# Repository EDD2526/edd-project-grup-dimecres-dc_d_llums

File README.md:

# Projecte Llums Cotxe

> **Autors:** Marcel Lleonart, Eric Ruiz, Josep Leyva
> **Versió:** 1.1
> **Eina de disseny:** KiCad 9.0 o superior

---

##  Objectiu

Desenvolupar un **sistema de control de llums per a un automòbil a escala de projecte**, gestionat mitjançant un microcontrolador. El sistema integra els principals subsistemes d'il·luminació d'un vehicle i permet el seu control manual i automàtic.

### Funcions principals

* Llums diürnes (**DRL**)
* Intermitents esquerre i dret
* Llums de creuament
* Llums de carretera
* Activació automàtica segons la llum ambiental

Cada canal incorpora:

* Etapa de potència amb MOSFET
* Resistència de gate i pull-down
* Control directe des del microcontrolador mitjançant GPIO

---

##  Diagrama de blocs

---

##  Descripció funcional dels blocs

###  Microcontrolador – PIC18F26Q83

Coordina tots els subsistemes de llum, processa les entrades dels sensors i gestiona les comunicacions externes. Disposa d'interfícies **CAN**, **I2C** i **USART** per a expansió, diagnosi i depuració.

###  Driver de llums diürnes (DRL)

Controla l'encesa automàtica de les llums diürnes mitjançant un MOSFET **AO3400A**. L'activació es realitza segons la lectura del sensor de llum ambiental.

###  Driver d'intermitents

Gestiona els intermitents esquerre i dret. El parpelleig es genera per programari utilitzant temporitzadors interns del microcontrolador.

###  Driver de llums de creuament

Permet el control ON/OFF de les llums de creuament amb protecció elèctrica individual.

###  Driver de llums de carretera

Controla les llums de carretera amb protecció mitjançant fusible. Compatible amb càrregues LED o halògenes de baixa potència.

### Sensor de llum ambiental

Mesura la il·luminació exterior i permet l'activació automàtica de les llums diürnes o altres funcions programades.

---

##  Especificacions tècniques

| Paràmetre              | Valor                                               |
| ---------------------- | --------------------------------------------------- |
| Alimentació principal  | 12 Vcc                                              |
| Alimentació lògica     | 3.3 V regulats                                      |
| Microcontrolador       | Pic24hj128gp502                                     |
| Comunicacions          | CAN, I2C, USART                                     |
| MOSFET de potència     | AO3400A (canal N, logic-level)                      |
| Nivell de control GPIO | 3.3 V                                               |
| Protecció              |resistència de gate + pull-down                      |

---

##  Assignació de GPIO

| Senyal            | Funció                         |
| ----------------- | ------------------------------ |
| `DRL_CTRL`        | Control de llums diürnes       |
| `TURN_LEFT_CTRL`  | Intermitent esquerre           |
| `TURN_RIGHT_CTRL` | Intermitent dret               |
| `LOW_BEAM_CTRL`   | Llums de creuament             |
| `HI_BEAM_CTRL`    | Llums de carretera             |
| `LIGHT_INT`       | Interrupció del sensor de llum |

---

##  Funcionalitats implementades

* Activació automàtica de les DRL segons la llum ambiental
* Control independent de llums de creuament i carretera
* Interfície de depuració per USART
* Arquitectura preparada per integració en xarxa CAN

---

##  Llista de materials (BOM)

| Component                     | Valor / Model              | Encapsulat         | Quantitat |
| ----------------------------- | -------------------------- | ------------------ | --------: |
| Microcontrolador              | Pic24hj128gp502            | SOIC-28            |         1 |
| MOSFET canal N                | AO3400A                    | SOT-23             |         8 |
| Regulador lineal              | LM1117-5.0                 | TO-252             |         1 |
| Resonador / Cristall          | 8 MHz                      | HC-49 o equivalent |         1 |
| Inductor                      | 33 µH                      | Radial             |         1 |
| Díodes de protecció           | Rectificador               | DO-201AD           |         9 |
| Condensadors de desacoblament | 100 nF                     | 0805               |         7 |
| Condensadors                  | 10 µF                      | 0805               |         3 |
| Condensador electrolític      | 680 µF                     | Radial             |         1 |
| Condensadors                  | 33 pF                      | 0805               |         2 |
| Condensador                   | 4.7 nF                     | 0805               |         1 |
| Resistències                  | 100 Ω                      | 0805               |         8 |
| Resistències                  | 10 kΩ                      | 0805               |  Diverses |
| Borns de connexió             | 2 vies, pas 5.08 mm        | Terminal Block     |        11 |
| Connector ICSP                | Programació PIC            | 2x03, 2.54 mm      |         1 |
| Interruptors SPDT             | Selector                   | Through-hole       |         5 |
| Polsador                      | Reset / funció             | 6 mm               |         1 |
| Sensor de llum                | TSL2561 (o equivalent I2C) | SMD                |         1 |

> **Nota:** La quantitat exacta d'alguns components passius pot variar segons la revisió del disseny i les opcions de muntatge.

---

##  Programació i configuració

### Perifèrics utilitzats

* GPIO digitals per al control de sortides
* I2C per al sensor de llum
* USART per a depuració i diagnosi
* CAN per a futures ampliacions

---

##  Proteccions incorporades

* Resistència sèrie a la gate dels MOSFET
* Resistència pull-down per evitar activacions espúries
* Filtrat de l'alimentació mitjançant condensadors de desacoblament
* Protecció davant transitoris de commutació

---

##  Aplicacions

Aquest projecte és ideal per a:

* Maquetes i prototips d'automoció
* Sistemes d'il·luminació intel·ligents
* Pràctiques de microcontroladors i electrònica de potència
* Desenvolupament de mòduls electrònics per automoció

---

##  Estat del projecte

**Versió actual:** 1.5

* ✅ Esquemàtic completat
* 🔄 PCB en desenvolupament i validació
* ✔️ BOM inicial verificada

---

##  Llicència

Aquest projecte ha estat desenvolupat amb finalitats educatives i acadèmiques.

---

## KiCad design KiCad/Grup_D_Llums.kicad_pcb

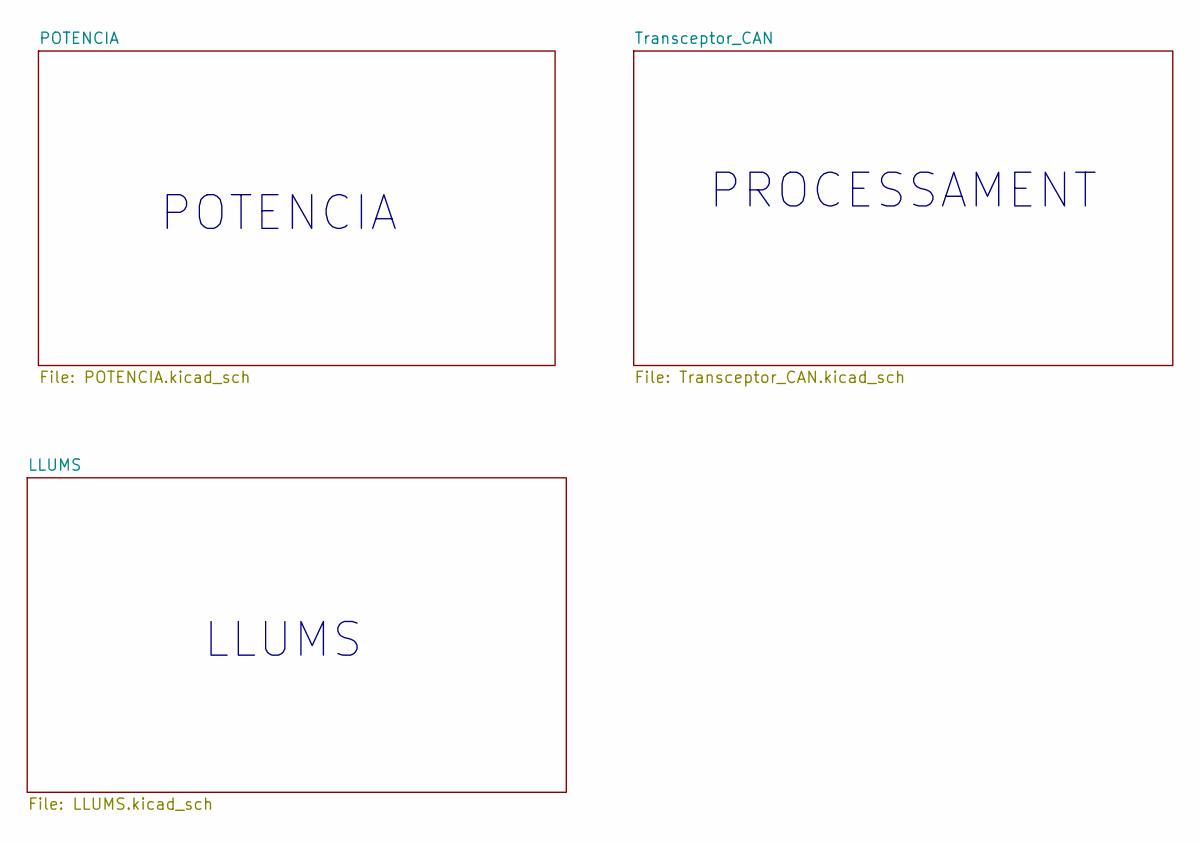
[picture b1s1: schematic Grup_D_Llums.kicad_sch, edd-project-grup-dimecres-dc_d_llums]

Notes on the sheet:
PROCESSAMENT
LLUMS
POTENCIA

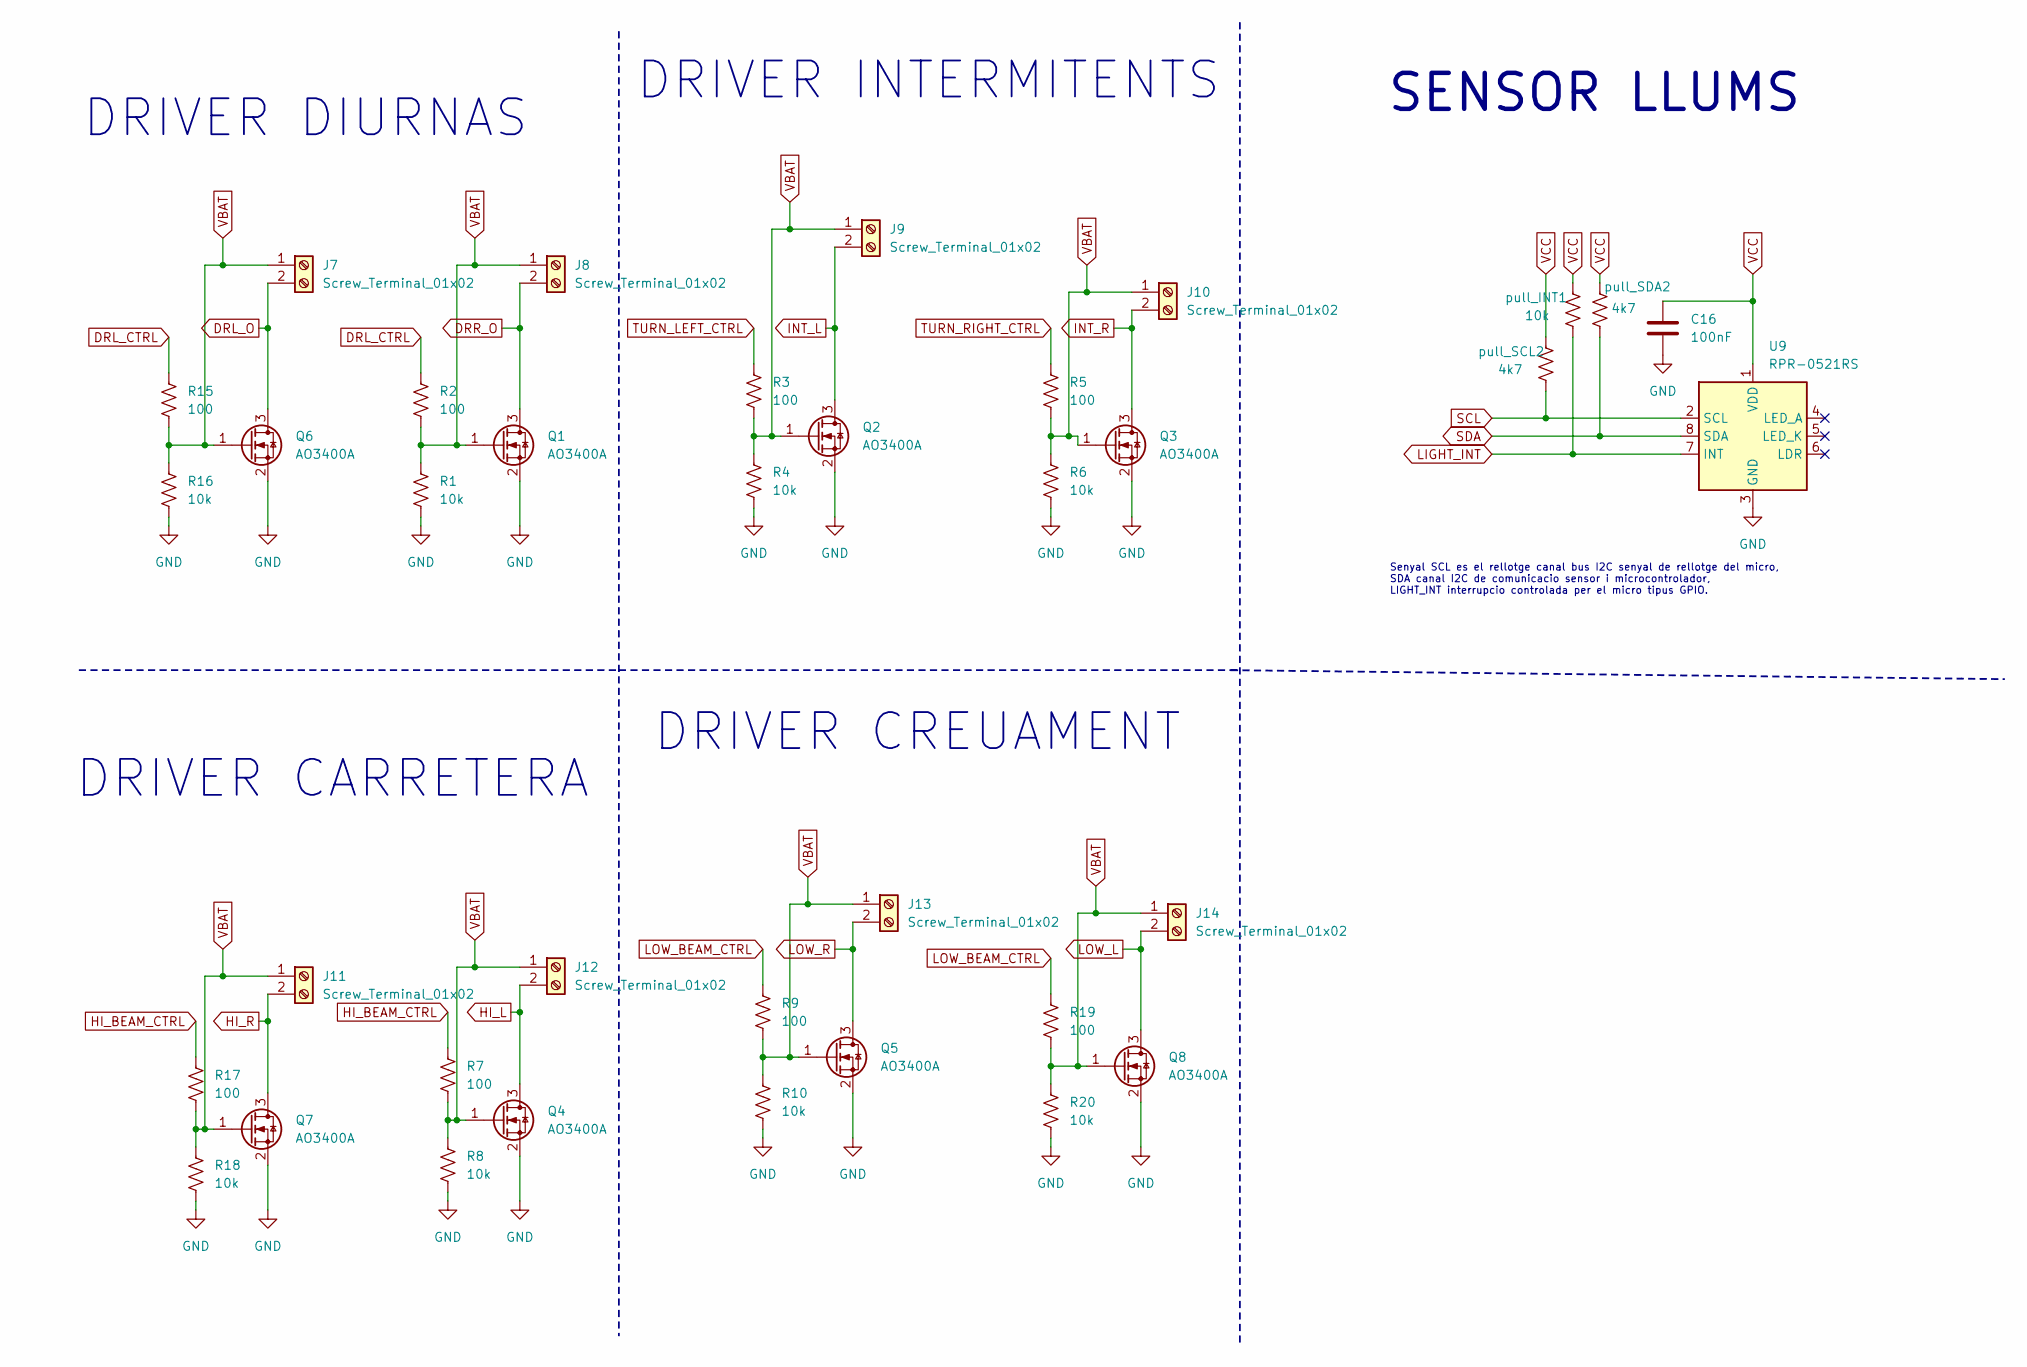
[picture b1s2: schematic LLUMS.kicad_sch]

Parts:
C16: 100nF; C_0805_2012Metric
J7, J8, J9, J10, J11, J12, J13, J14: Screw_Terminal_01x02; TerminalBlock_Phoenix_MKDS-1,5-2-5.08_1x02_P5.08mm_Horizont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
Q1, Q2, Q3, Q4, Q5, Q6, Q7, Q8: AO3400A; SOT-23
R1, R4, R6, R8, R10, R16, R18, R20: 10k; R_0805_2012Metric
R2, R3, R5, R7, R9, R15, R17, R19: 100; R_0805_2012Metric
U9: RPR-0521RS; Rohm_RPR-0521RS
pull_INT1: 10k; R_0805_2012Metric
pull_SCL2: 4k7; R_0805_2012Metric
pull_SDA2: 4k7; R_0805_2012Metric

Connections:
DRL_CTRL: R2.1, R15.1; also elsewhere on the board
DRL_O: J7.2, Q6.3 (D)
DRR_O: J8.2, Q1.3 (D)
GND: C16.2, Q1.2 (S), Q2.2 (S), Q3.2 (S), Q4.2 (S), Q5.2 (S), Q6.2 (S), Q7.2 (S), Q8.2 (S), R1.2, R4.2, R6.2, R8.2, R10.2, R16.2, R18.2, R20.2, U9.3 (GND); also elsewhere on the board
HI_BEAM_CTRL: R7.1, R17.1; also elsewhere on the board
HI_L: J12.2, Q4.3 (D)
HI_R: J11.2, Q7.3 (D)
INT_L: J9.2, Q2.3 (D)
INT_R: J10.2, Q3.3 (D)
LIGHT_INT: U9.7 (INT), pull_INT1.2; also elsewhere on the board
LOW_BEAM_CTRL: R9.1, R19.1; also elsewhere on the board
LOW_L: J14.2, Q8.3 (D)
LOW_R: J13.2, Q5.3 (D)
SCL: U9.2 (SCL), pull_SCL2.2; also elsewhere on the board
SDA: U9.8 (SDA), pull_SDA2.2; also elsewhere on the board
TURN_LEFT_CTRL: R3.1; also elsewhere on the board
TURN_RIGHT_CTRL: R5.1; also elsewhere on the board
VBAT: J7.1, J8.1, J9.1, J10.1, J11.1, J12.1, J13.1, J14.1, Q1.1 (G), Q2.1 (G), Q3.1 (G), Q4.1 (G), Q5.1 (G), Q6.1 (G), Q7.1 (G), Q8.1 (G), R1.1, R2.2, R3.2, R4.1, R5.2, R6.1, R7.2, R8.1, R9.2, R10.1, R15.2, R16.1, R17.2, R18.1, R19.2, R20.1; also elsewhere on the board
VCC: C16.1, U9.1 (VDD), pull_INT1.1, pull_SCL2.1, pull_SDA2.1; also elsewhere on the board

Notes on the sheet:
DRIVER INTERMITENTS
SENSOR LLUMS
DRIVER CREUAMENT
DRIVER DIURNAS
DRIVER CARRETERA
Senyal SCL es el rellotge canal bus I2C senyal de rellotge del micro, SDA canal I2C de comunicacio sensor i microcontrolador, LIGHT_INT interrupcio controlada per el micro tipus GPIO.

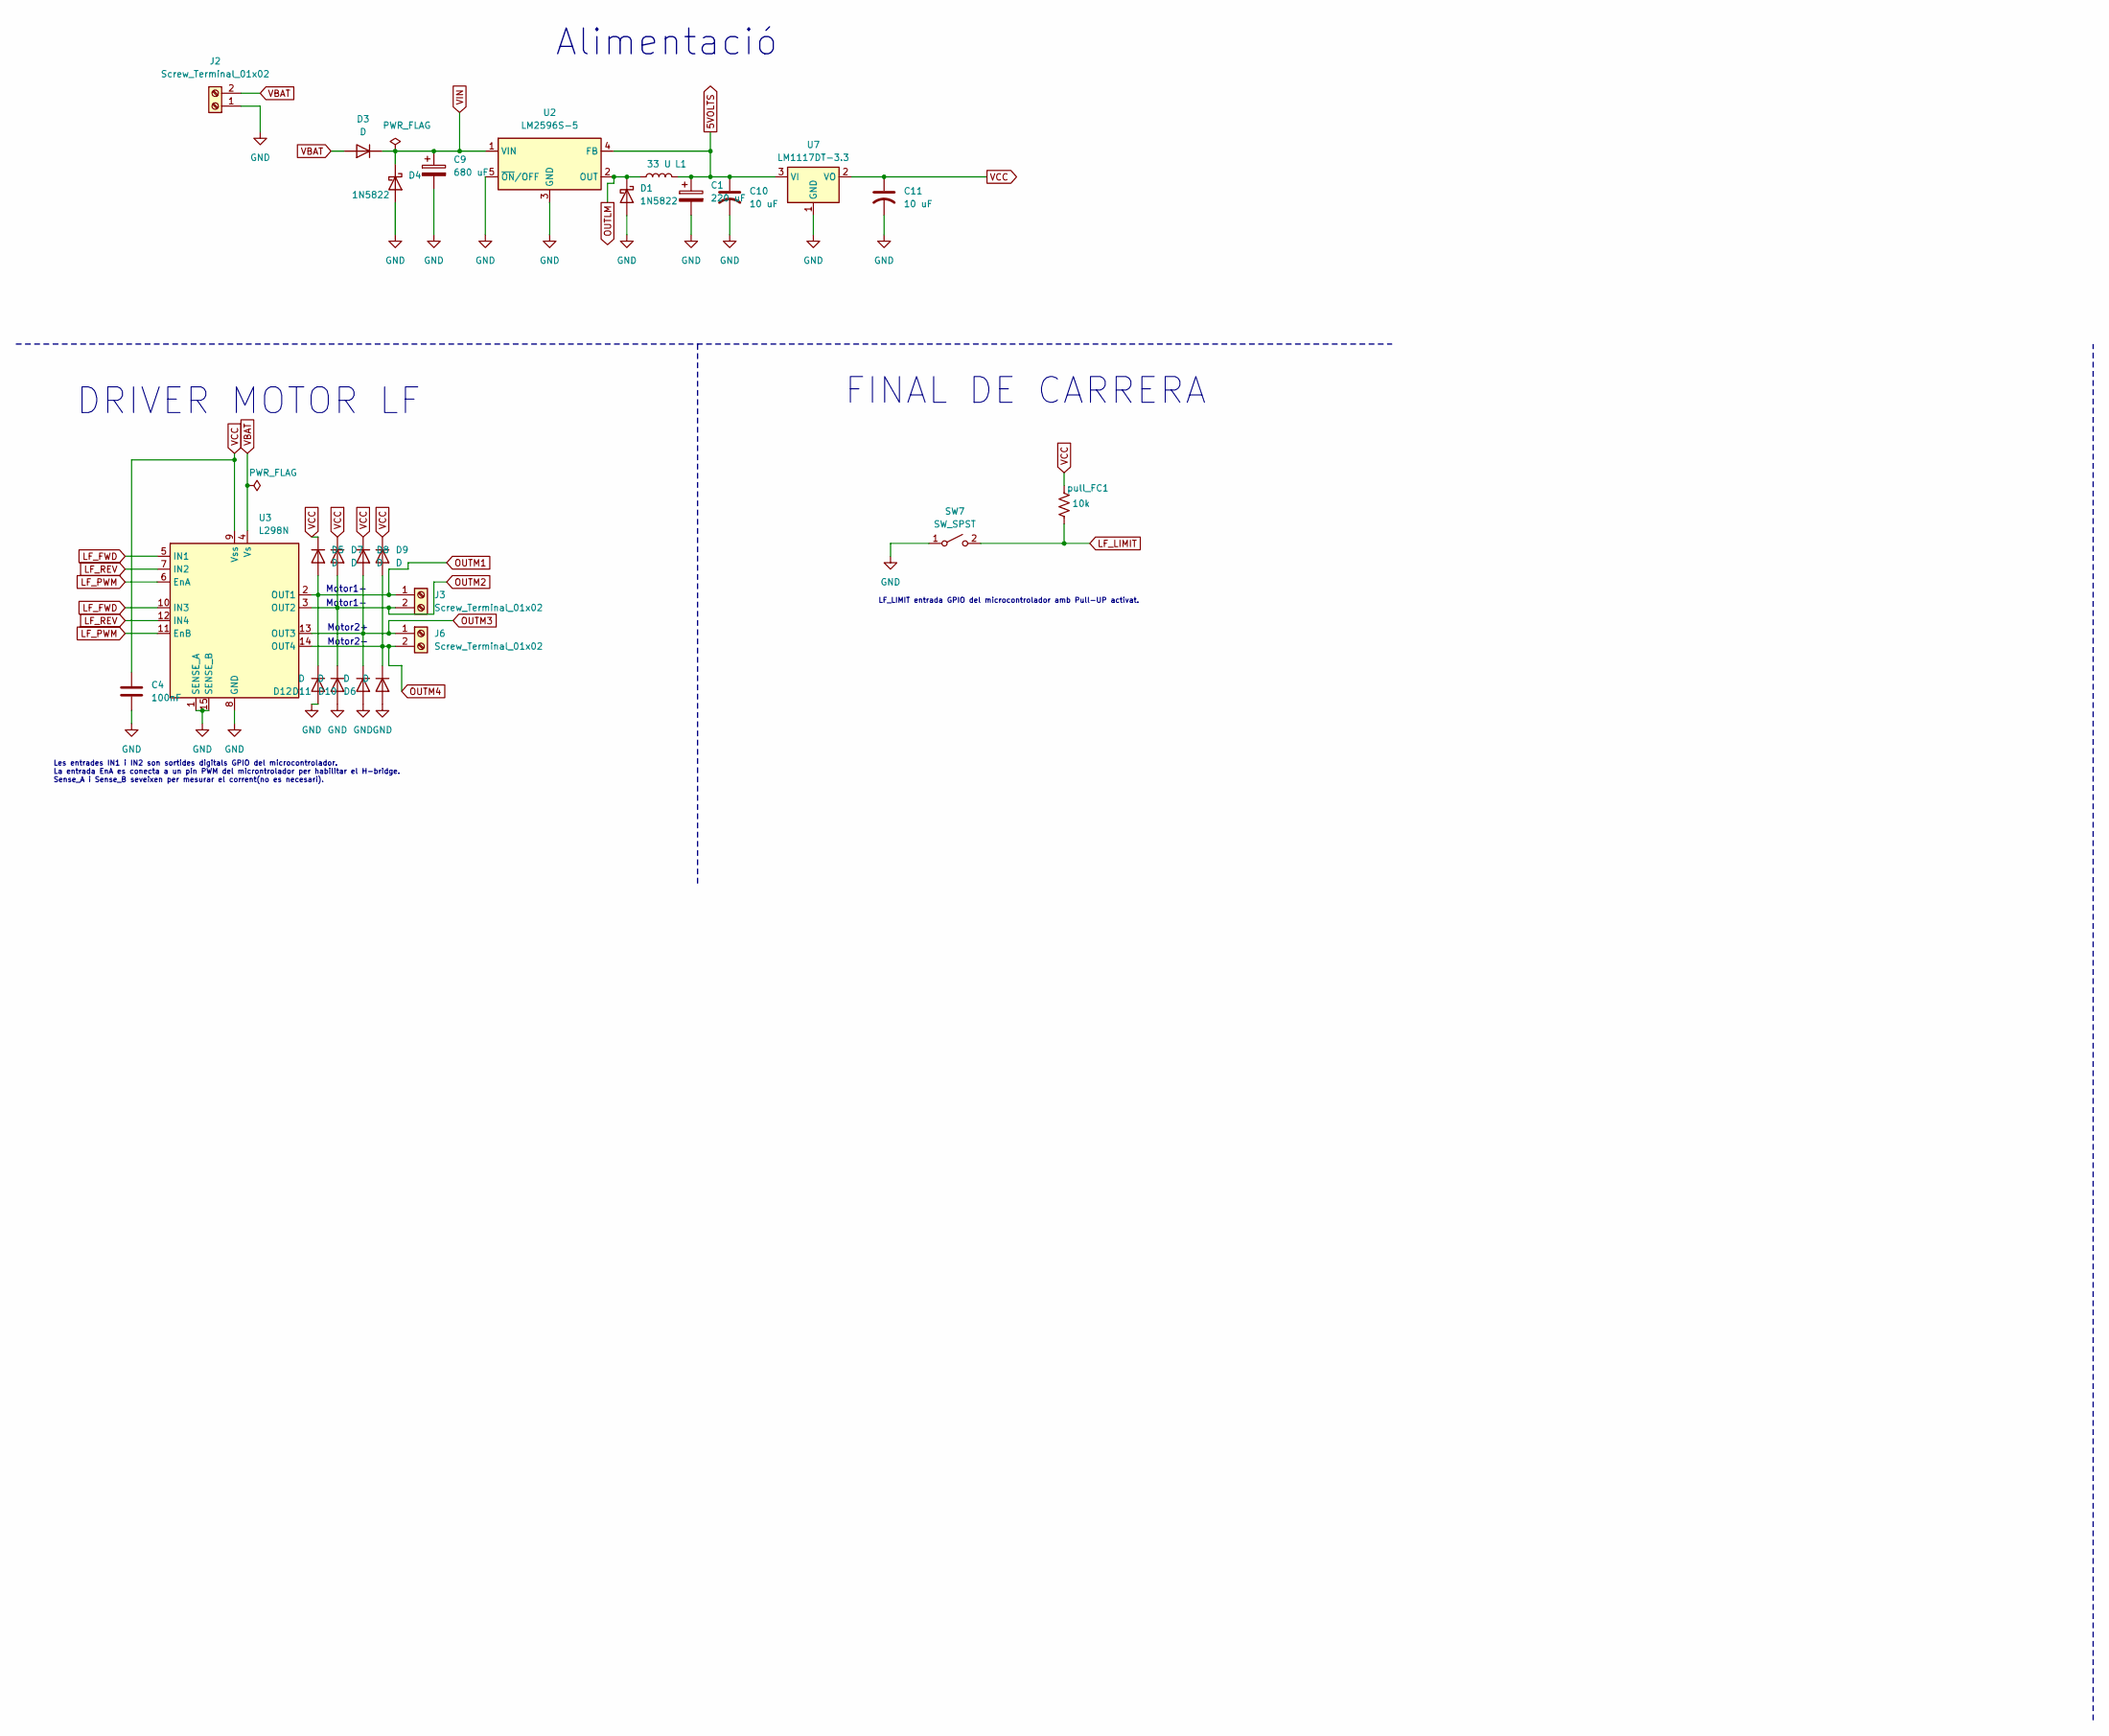
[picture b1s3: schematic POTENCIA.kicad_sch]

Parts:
C1: 220 uF; CP_Radial_D8.0mm_P3.50mm
C4: 100nF; C_0805_2012Metric
C9: 680 uF; CP_Radial_D10.0mm_P5.00mm
C10, C11: 10 uF; C_0805_2012Metric
D1, D4: 1N5822; D_DO-201AD_P15.24mm_Horizontal
D3, D5, D6, D7, D8, D9, D10, D11, D12: D; D_DO-201AD_P15.24mm_Horizontal
J2, J3, J6: Screw_Terminal_01x02; TerminalBlock_Phoenix_MKDS-1,5-2-5.08_1x02_P5.08mm_Horizont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
L1: 33 U; L_Radial_D10.0mm_P5.00mm_Fastron_07M
SW7: SW_SPST; SW_PUSH_6mm
U2: LM2596S-5; TO-263-5_TabPin3
U3: L298N; TO-220-15_P2.54x5.08mm_StaggerOdd_Lead4.58mm_Vertical
U7: LM1117DT-3.3; TO-252-3_TabPin2
pull_FC1: 10k; R_0805_2012Metric

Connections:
5VOLTS: C1.1, C10.1, L1.2, U2.4 (FB), U7.3 (VI)
GND: C1.2, C4.2, C9.2, C10.2, C11.2, D1.2 (A), D4.2 (A), D6.2 (A), D10.2 (A), D11.2 (A), D12.2 (A), J2.1, SW7.1 (A), U2.3 (GND), U2.5 (~ON/OFF), U3.1 (SENSE_A), U3.8 (GND), U3.15 (SENSE_B), U7.1 (GND); also elsewhere on the board
LF_FWD: U3.5 (IN1), U3.10 (IN3); also elsewhere on the board
LF_LIMIT: SW7.2 (B), pull_FC1.2; also elsewhere on the board
LF_PWM: U3.6 (EnA), U3.11 (EnB); also elsewhere on the board
LF_REV: U3.7 (IN2), U3.12 (IN4); also elsewhere on the board
OUTLM: D1.1 (K), L1.1, U2.2 (OUT)
OUTM1: D5.2 (A), D12.1 (K), J3.1, U3.2 (OUT1)
OUTM2: D7.2 (A), D11.1 (K), J3.2, U3.3 (OUT2)
OUTM3: D8.2 (A), D10.1 (K), J6.1, U3.13 (OUT3)
OUTM4: D6.1 (K), D9.2 (A), J6.2, U3.14 (OUT4)
VBAT: D3.2 (A), J2.2, U3.4 (Vs); also elsewhere on the board
VCC: C4.1, C11.1, D5.1 (K), D7.1 (K), D8.1 (K), D9.1 (K), U3.9 (Vss), U7.2 (VO), pull_FC1.1; also elsewhere on the board
VIN: C9.1, D3.1 (K), D4.1 (K), U2.1 (VIN)

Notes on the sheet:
Les entrades IN1 i IN2 son sortides digitals GPIO del microcontrolador. La entrada EnA es conecta a un pin PWM del microntrolador per habilitar el H-bridge. Sense_A i Sense_B seveixen per mesurar el corrent(no es necesari).
Alimentació
Motor2-
FINAL DE CARRERA
Motor1+
Motor2+
DRIVER MOTOR LF
Motor1-
LF_LIMIT entrada GPIO del microcontrolador amb Pull-UP activat.

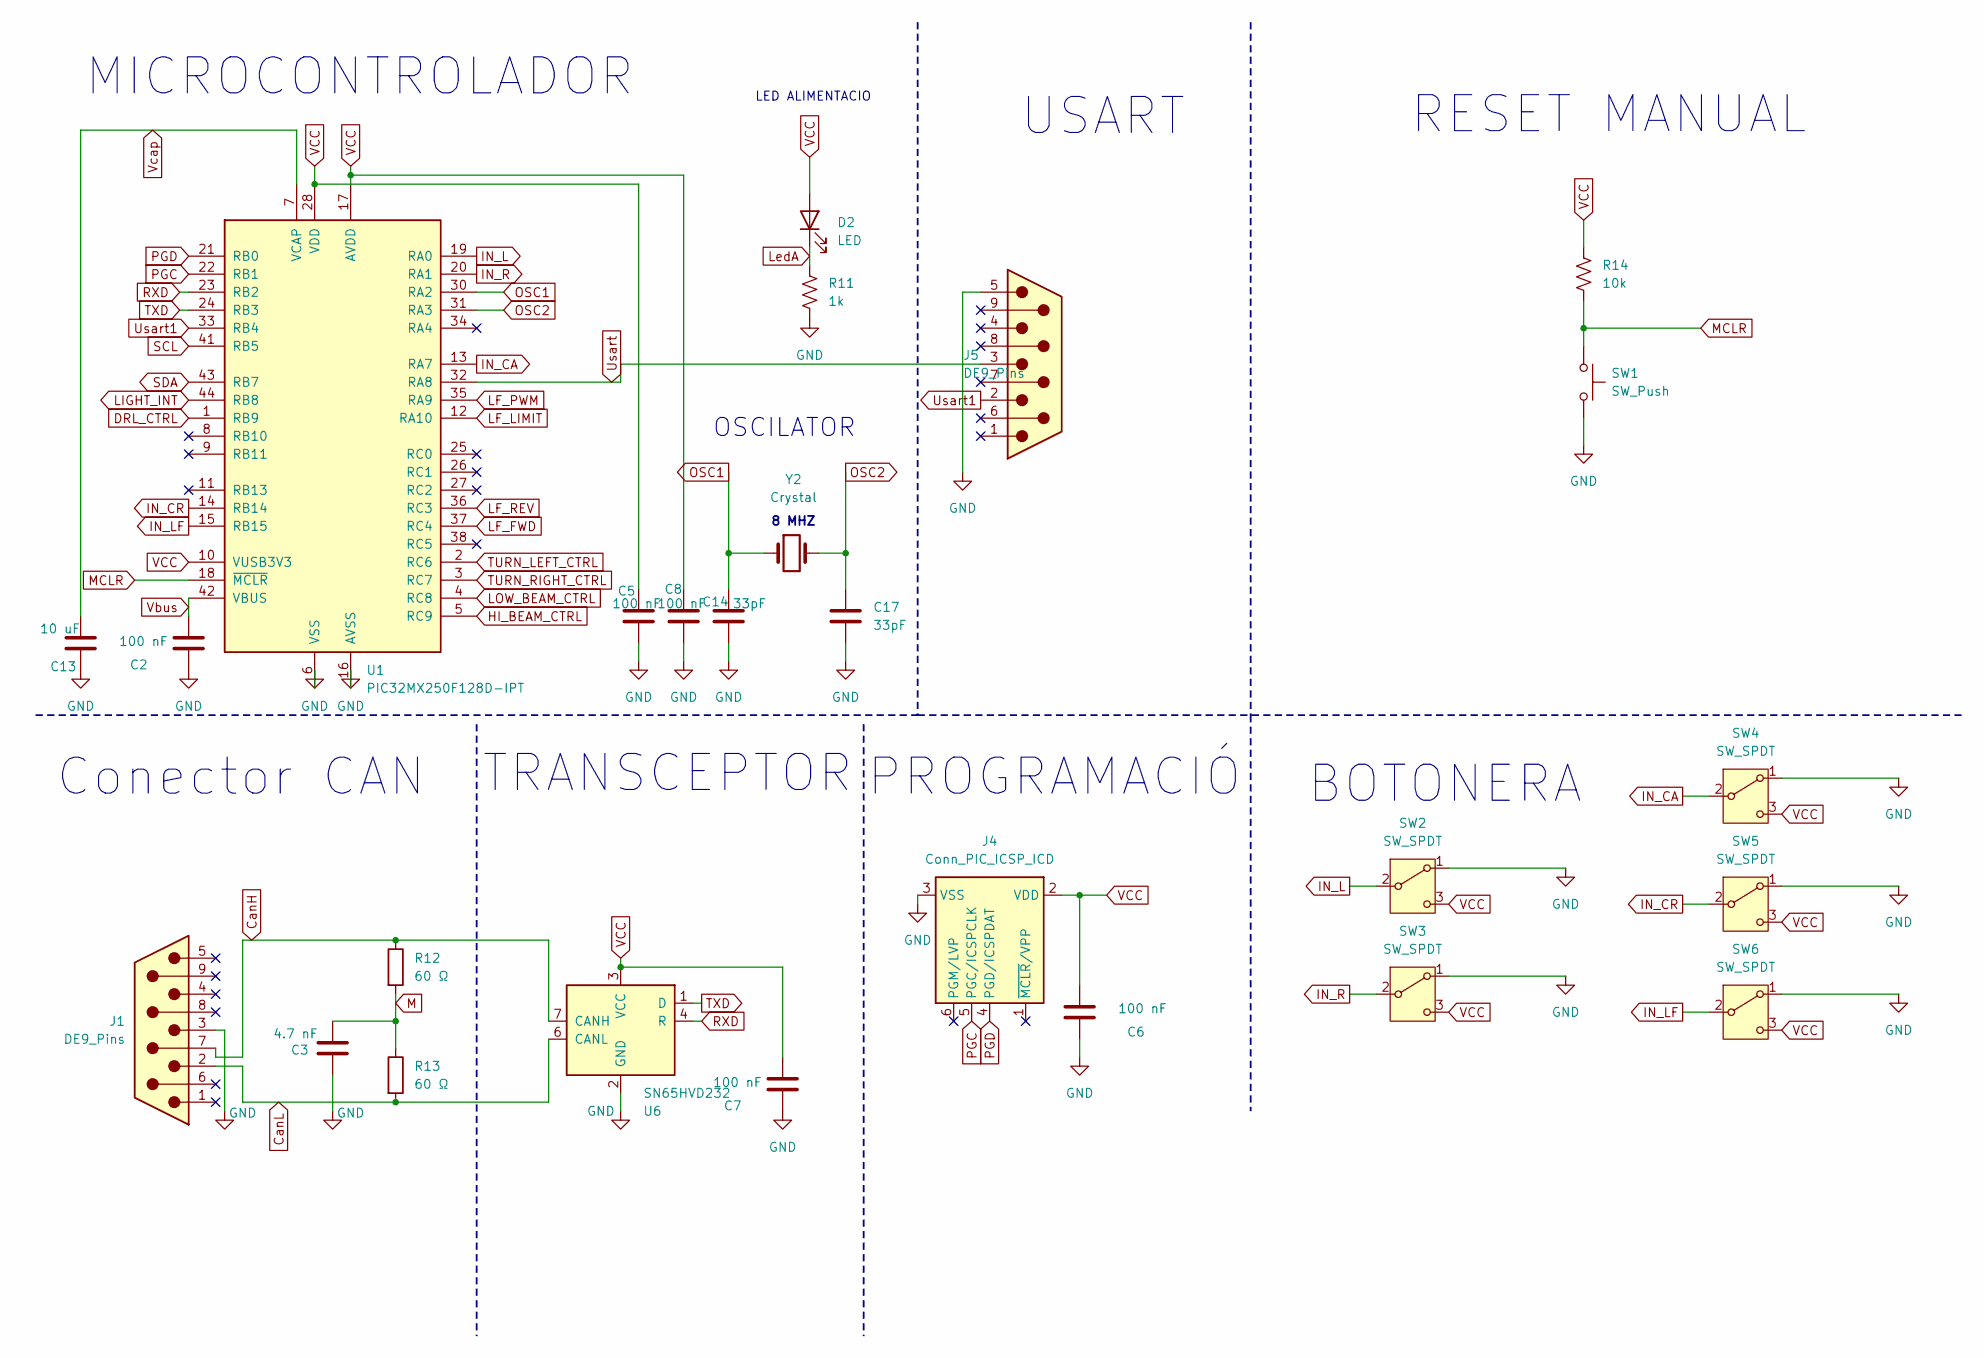
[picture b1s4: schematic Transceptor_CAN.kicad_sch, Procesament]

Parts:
C2, C5, C6, C7, C8: 100 nF; C_0805_2012Metric
C3: 4.7 nF; C_0805_2012Metric
C13: 10 uF; C_0805_2012Metric
C14, C17: 33pF; C_0805_2012Metric
D2: LED; LED_0805_2012Metric_Pad1.15x1.40mm_HandSolder
J1, J5: DE9_Pins; DSUB-9_Socket_Horizontal_P2.77x2.84mm_EdgePinOffset9.40mm
J4: Conn_PIC_ICSP_ICD; PinHeader_2x03_P2.54mm_Vertical
R11: 1k; R_0805_2012Metric
R12, R13: 60 Ω; R_0603_1608Metric
R14: 10k; R_0805_2012Metric
SW1: SW_Push; SW_Push_1P1T-SH_NO_CK_KMR2xxG
SW2, SW3, SW4, SW5, SW6: SW_SPDT; SW_SPDT_CK_JS102011SAQN
U1: PIC32MX250F128D-IPT; TQFP-44_10x10mm_P0.8mm
U6: SN65HVD232; SOIC-8_3.9x4.9mm_P1.27mm
Y2: Crystal; Crystal_HC49-U_Vertical

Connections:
CanH: J1.7, R12.1, U6.7 (CANH)
CanL: J1.2, R13.2, U6.6 (CANL)
DRL_CTRL: U1.1 (RB9); also elsewhere on the board
GND: C2.2, C3.1, C5.2, C6.2, C7.2, C8.2, C13.1, C14.2, C17.2, J1.3, J4.3 (VSS), J5.5, R11.2, SW1.2, SW2.1 (A), SW3.1 (A), SW4.1 (A), SW5.1 (A), SW6.1 (A), U1.6 (VSS), U1.16 (AVSS), U1.29 (VSS), U1.39 (VSS), U6.2 (GND); also elsewhere on the board
HI_BEAM_CTRL: U1.5 (RC9); also elsewhere on the board
IN_CA: SW4.2 (B), U1.13 (RA7)
IN_CR: SW5.2 (B), U1.14 (RB14)
IN_L: SW2.2 (B), U1.19 (RA0)
IN_LF: SW6.2 (B), U1.15 (RB15)
IN_R: SW3.2 (B), U1.20 (RA1)
LF_FWD: U1.37 (RC4); also elsewhere on the board
LF_LIMIT: U1.12 (RA10); also elsewhere on the board
LF_PWM: U1.35 (RA9); also elsewhere on the board
LF_REV: U1.36 (RC3); also elsewhere on the board
LIGHT_INT: U1.44 (RB8); also elsewhere on the board
LOW_BEAM_CTRL: U1.4 (RC8); also elsewhere on the board
LedA: D2.1 (K), R11.1
M: C3.2, R12.2, R13.1
MCLR: R14.2, SW1.1, U1.18 (~MCLR)
OSC1: C14.1, U1.30 (RA2), Y2.1
OSC2: C17.1, U1.31 (RA3), Y2.2
PGC: J4.5 (PGC/ICSPCLK), U1.22 (RB1)
PGD: J4.4 (PGD/ICSPDAT), U1.21 (RB0)
RXD: U1.23 (RB2), U6.4 (R)
SCL: U1.41 (RB5); also elsewhere on the board
SDA: U1.43 (RB7); also elsewhere on the board
TURN_LEFT_CTRL: U1.2 (RC6); also elsewhere on the board
TURN_RIGHT_CTRL: U1.3 (RC7); also elsewhere on the board
TXD: U1.24 (RB3), U6.1 (D)
Usart: J5.3, U1.32 (RA8)
Usart1: J5.2, U1.33 (RB4)
VCC: C5.1, C6.1, C7.1, C8.1, D2.2 (A), J4.2 (VDD), R14.1, SW2.3 (C), SW3.3 (C), SW4.3 (C), SW5.3 (C), SW6.3 (C), U1.10 (VUSB3V3), U1.17 (AVDD), U1.28 (VDD), U1.40 (VDD), U6.3 (VCC); also elsewhere on the board
Vbus: C2.1, U1.42 (VBUS)
Vcap: C13.2, U1.7 (VCAP)

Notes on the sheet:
MICROCONTROLADOR
PROGRAMACIÓ
BOTONERA
8 MHZ
USART
RESET MANUAL
Conector CAN
TRANSCEPTOR
OSCILATOR
LED ALIMENTACIO

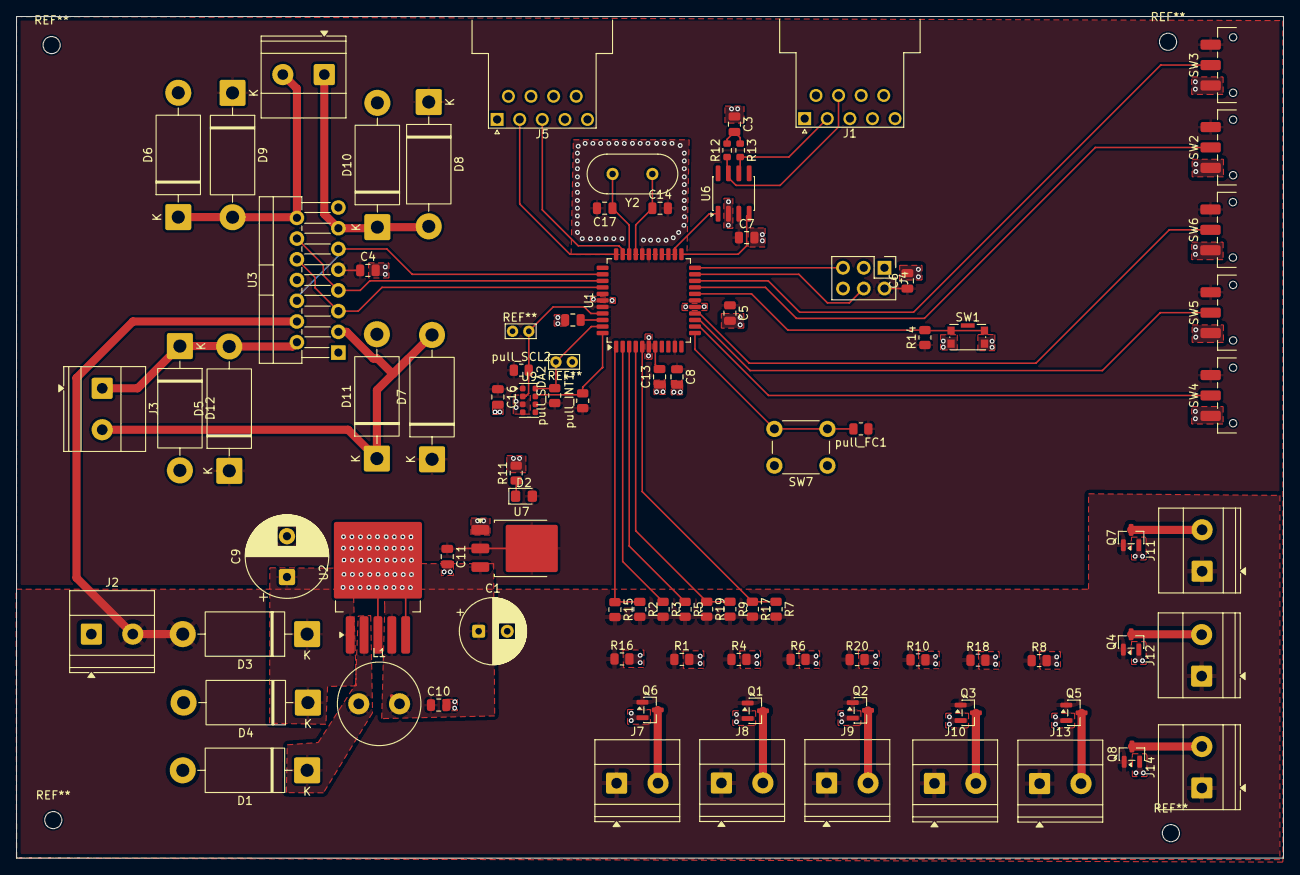
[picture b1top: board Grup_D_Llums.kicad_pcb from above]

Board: 2 copper layers, 155.3 x 103.2 mm, 88 parts (0 on the bottom side), 50 nets.

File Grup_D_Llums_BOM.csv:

"Id";"Identificador";"Huella";"Cantidad";"Identificación";"Suministrador y ref";
1;"C11,C13,C10";"C_0805_2012Metric";3;"10 uF";;;
2;"R17,R19,R3,R9,R2,R7,R15,R5";"R_0805_2012Metric";8;"100";;;
3;"J12,J7,J6,J11,J10,J13,J8,J2,J14,J3,J9";"TerminalBlock_Phoenix_MKDS-1,5-2-5.08_1x02_P5.08mm_Horizontal";11;"Screw_Terminal_01x02";;;
4;"J4";"PinHeader_2x03_P2.54mm_Vertical";1;"Conn_PIC_ICSP_ICD";;;
5;"Q6,Q4,Q8,Q2,Q3,Q5,Q7,Q1";"SOT-23";8;"AO3400A";;;
6;"C8,C6,C2,C5,C7";"C_0805_2012Metric";5;"100 nF";;;
7;"L1";"L_Radial_D10.0mm_P5.00mm_Fastron_07M";1;"33 U";;;
8;"C16,C4";"C_0805_2012Metric";2;"100nF";;;
9;"SW2,SW6,SW4,SW5,SW3";"SW_SPDT_CK_JS102011SAQN";5;"SW_SPDT";;;
10;"C9";"CP_Radial_D10.0mm_P5.00mm";1;"680 uF";;;
11;"Y2";"Crystal_HC49-U_Vertical";1;"Crystal";;;
12;"D5,D3,D7,D11,D9,D10,D6,D8,D12";"D_DO-201AD_P15.24mm_Horizontal";9;"D";;;
13;"SW7";"SW_PUSH_6mm";1;"SW_SPST";;;
14;"C14,C17";"C_0805_2012Metric";2;"33pF";;;
15;"C3";"C_0805_2012Metric";1;"4.7 nF";;;
16;"U7";"TO-252-3_TabPin2";1;"LM1117DT-3.3";;;
17;"R8,pull_FC1,pull_INT1,R4,R18,R20,R16,R1,R14,R6,R10";"R_0805_2012Metric";11;"10k";;;
18;"J1,J5";"DSUB-9_Socket_Horizontal_P2.77x2.84mm_EdgePinOffset9.40mm";2;"DE9_Pins";;;
19;"U9";"Rohm_RPR-0521RS";1;"RPR-0521RS";;;
20;"U2";"TO-263-5_TabPin3";1;"LM2596S-5";;;
21;"U6";"SOIC-8_3.9x4.9mm_P1.27mm";1;"SN65HVD232";;;
22;"U3";"TO-220-15_P2.54x5.08mm_StaggerOdd_Lead4.58mm_Vertical";1;"L298N";;;
23;"D2";"LED_0805_2012Metric";1;"LED";;;
24;"C1";"CP_Radial_D8.0mm_P3.50mm";1;"220 uF";;;
25;"pull_SCL2,pull_SDA2";"R_0805_2012Metric";2;"4k7";;;
26;"R11";"R_0805_2012Metric";1;"1k";;;
27;"U1";"TQFP-44_10x10mm_P0.8mm";1;"PIC32MX250F128D-IPT";;;
28;"R12,R13";"R_0603_1608Metric";2;"60 Ω";;;
29;"SW1";"SW_Push_1P1T-SH_NO_CK_KMR2xxG";1;"SW_Push";;;
30;"D4,D1";"D_DO-201AD_P15.24mm_Horizontal";2;"1N5822";;;

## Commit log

2026-03-11 Prova_1
2026-03-11 Update README.md
    Prova 2
2026-03-11 Projecte kicad creat
2026-03-11 Nombres autors i nombre projecte
2026-03-16 Raiz main creada
2026-03-16 Deleted useless documents
2026-03-16 Implementacio Drivers Motor Neteja fars
2026-03-16 Transceptor CAN 1
2026-03-16 Alimentcaio
2026-03-16 Solucionando problemas del esquematic
2026-03-16 Backlink to CADLAB.io has been added.
2026-03-17 Carpeta de Datasheets para tener acceso rapido a la informacion de cada componente
2026-03-17 Prueba
2026-03-17 Prova 2
2026-03-17 Arreglando cosas
2026-03-17 Capacitat DC/DC
2026-03-17 Sensor llums afegit
2026-03-17 nada
2026-03-17 Driver Diurna hecho
2026-03-17 Microchip afegit
2026-03-17 Datasheet update
2026-03-17 Driver llums fet
2026-03-17 Communicacio afegida
2026-03-17 Procesament i comunicació
2026-03-17 botonera, datashet usart
2026-03-17 Programador
2026-03-17 Update README.md
    Diagrama de bloc
2026-03-18 acabar can, estil y micro biel
2026-03-18 Debugging
2026-03-23 Alimentació arreglada
2026-03-23 Arreglat errors de schematic version 1
2026-03-23 Pequeño error
2026-03-23 frecuencia del reloj
2026-03-23 titulos
2026-03-23 Update README.md
    Josep si lees esto happens
2026-03-25 Bloc processament
2026-04-05 Huellass
2026-04-05 lil hotfix
2026-04-05 Hotfix for driver leds
2026-04-06 Pulsador Reset manual
2026-04-06 Some placement
2026-04-07 Placa
2026-04-08 Hello
2026-04-08 PCB Hotfixes
2026-04-14 B, ground
2026-04-14 grund c
2026-04-15 Hotfixes
2026-04-15 PCB FIXIng
2026-04-15 Ayuda
2026-04-15 jeje
2026-04-15 hotfix
2026-04-23 fin1
2026-04-28 Update README.md
    a
2026-04-28 Finished
